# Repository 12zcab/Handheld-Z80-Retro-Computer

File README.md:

# A Handheld Z80 Retro Computer

Hello Im 12zcab from Hong Kong and I designed this Z80 Retro Computer :DD

# Zine Page
https://www.figma.com/design/0DzeSIebLkugrNq00bVcSF/Untitled?node-id=0-1&t=Gd1BAF2dvagKk23V-1

# Images

# What is this?
This is a portable handheld computer made with z80 customized for assembly language programming and simplified system for educational purpose.
The computer comtains a Z80 cpu,a SPI screen,a Esp32 C3 Supermini and 2 EEPROM slot,a RAM slot,a buzzer,some leds,2 7segments and a extendable port for IO.
The computer support Dual-UART communication, one with the Esp32 and one for extending.
# What it does?
It just let you run simple programs on it and let you bring it anywhere!
My final goal is to write a fully functional Operating System and make it as simple as possible on this computer!
With the ESP32 C3 Supermini connected through UART,you can draw on SPI screen and output characters just like connected to a VT100 Terminal (for old computers)
With the Buzzer,7segments and the keyboard also with the extendable port,you can build alsome retro coding projects on this old-fashion Cyberdeck :D
# Why it exists?
Erm it all started when I found a video about old pokemon games and i started to play Gen 1 pokemon games on emulators(Red Version).
I found it a really amazing experience to have play a game with greyscale and 8 bit musics.
Then I asked my parents and found that we actually have a real gameboy athome!!
I then started to research on how gameboy works and study on the Disassembled PokeRed gameboy assembly code on github and I was shocked on how elegance it is the original assembly code.
Then I learnt the gbz80 instruction set,also the boot rom of the gameboy,then also 8086,8051,8085 and z80 assembly.
I followed a youtube video and built my first z80 computer and started to do a few assembly programming on it and yah its really fun [Ytlink](https://youtu.be/A0VpPRWrqHc?si=ajm_OGpBwFbzzyzW).
I recently found Fallout Event on HackClub and instantly found this a great oppertunity to design my own real z80 computer that is simple and workable.

# Basic Structure
##Memory Map
| Address | Compoenent | Function |
|----|----|----|
|0x0000 - 0x7FFF| EEPROM | Executable Code of Operating System |
|0x8000 - 0xFEFF| RAM or EEPROM | Multibanked External EEPROM and RAM |
|0xFF00 - 0xFFFF| IO Outputs | for Output,UART,and also other Extension Usage |
|----|----|----|

# Compoenents

## Main Compoenents
| Name | Usage | Quantity |
|----|----|----|
| Z84C00xxP | The CPU of the Computer | 1 |
| ESP32 C3 Supermini | The Micro Controller Board for Serial Output Processing | 1 |
| 3.5inch SPI Screen 14Pin| For Displaying Serial Output | 1 |
| DS12885+ Clock Module | Clock Module For Z80 | 1 |
| 62256 | 32k RAM for Z80 | 1 |
| 28C256 | 32k EEPROM for External file and Bootloader and Applications | 2 |
| HDSP-7501 | 7 Segment Display for Z80 Output | 2 |
| 16550 | UART Communication IC for Z80 IO | 2 |
| PTS 810 SMD Button | Keyboard Input for Z80 | 64 |
| 4 Pin 6mm Switch | Reset Button for Z80 | 1 |
| LED SMD 1206 | SMD LED with internal resistor for Signal and Data Bus displaying | 39 |
| Buzzer | D12mm height 9.5mm with RM7.6mm Buzzer for ESP32 C3 Supermini to Emit sound when receive specific serial input from Z80 | 1 |
| CR2032 battery holder | Battery for DS12885+ Clock Module | 1 |

## Logic Gates and ICs
| Name | Usage | Quantity |
|----|----|----|
| 74HC573 | A Registor for Input and Output and Multibanking | 5 |
| 74HC04 | Hex Logic Invertor for toggling High-Activate Signals and Low-Activate Signals | 2 |
| 4068 | 8 Input AND/NAND Logic Gate for IO Signal Filtering | 1 |
| 74154 | 4 to 16 Decoder for IOS Address Decoding | 1 |
| 74HC00 | Quad NAND Gate | 2 |

## Crystals
| Name | Usage | Quantity |
|----|----|----|
| 4 Pin Crystals | 20MHz and 1.8432MHz for CPU and UART ic respectively | 2 |
| 2 Pin Crystal | 32768Hz for DS12885+ Clock Module | 1 |

## Resistors
| Name | Usage | Quantity |
|----|----|----|
| 1K resistor | 7 segment display resistor to prevent the display BURn :D | 2 |
| 10K resistor | Pull-up Resistors | 4 |

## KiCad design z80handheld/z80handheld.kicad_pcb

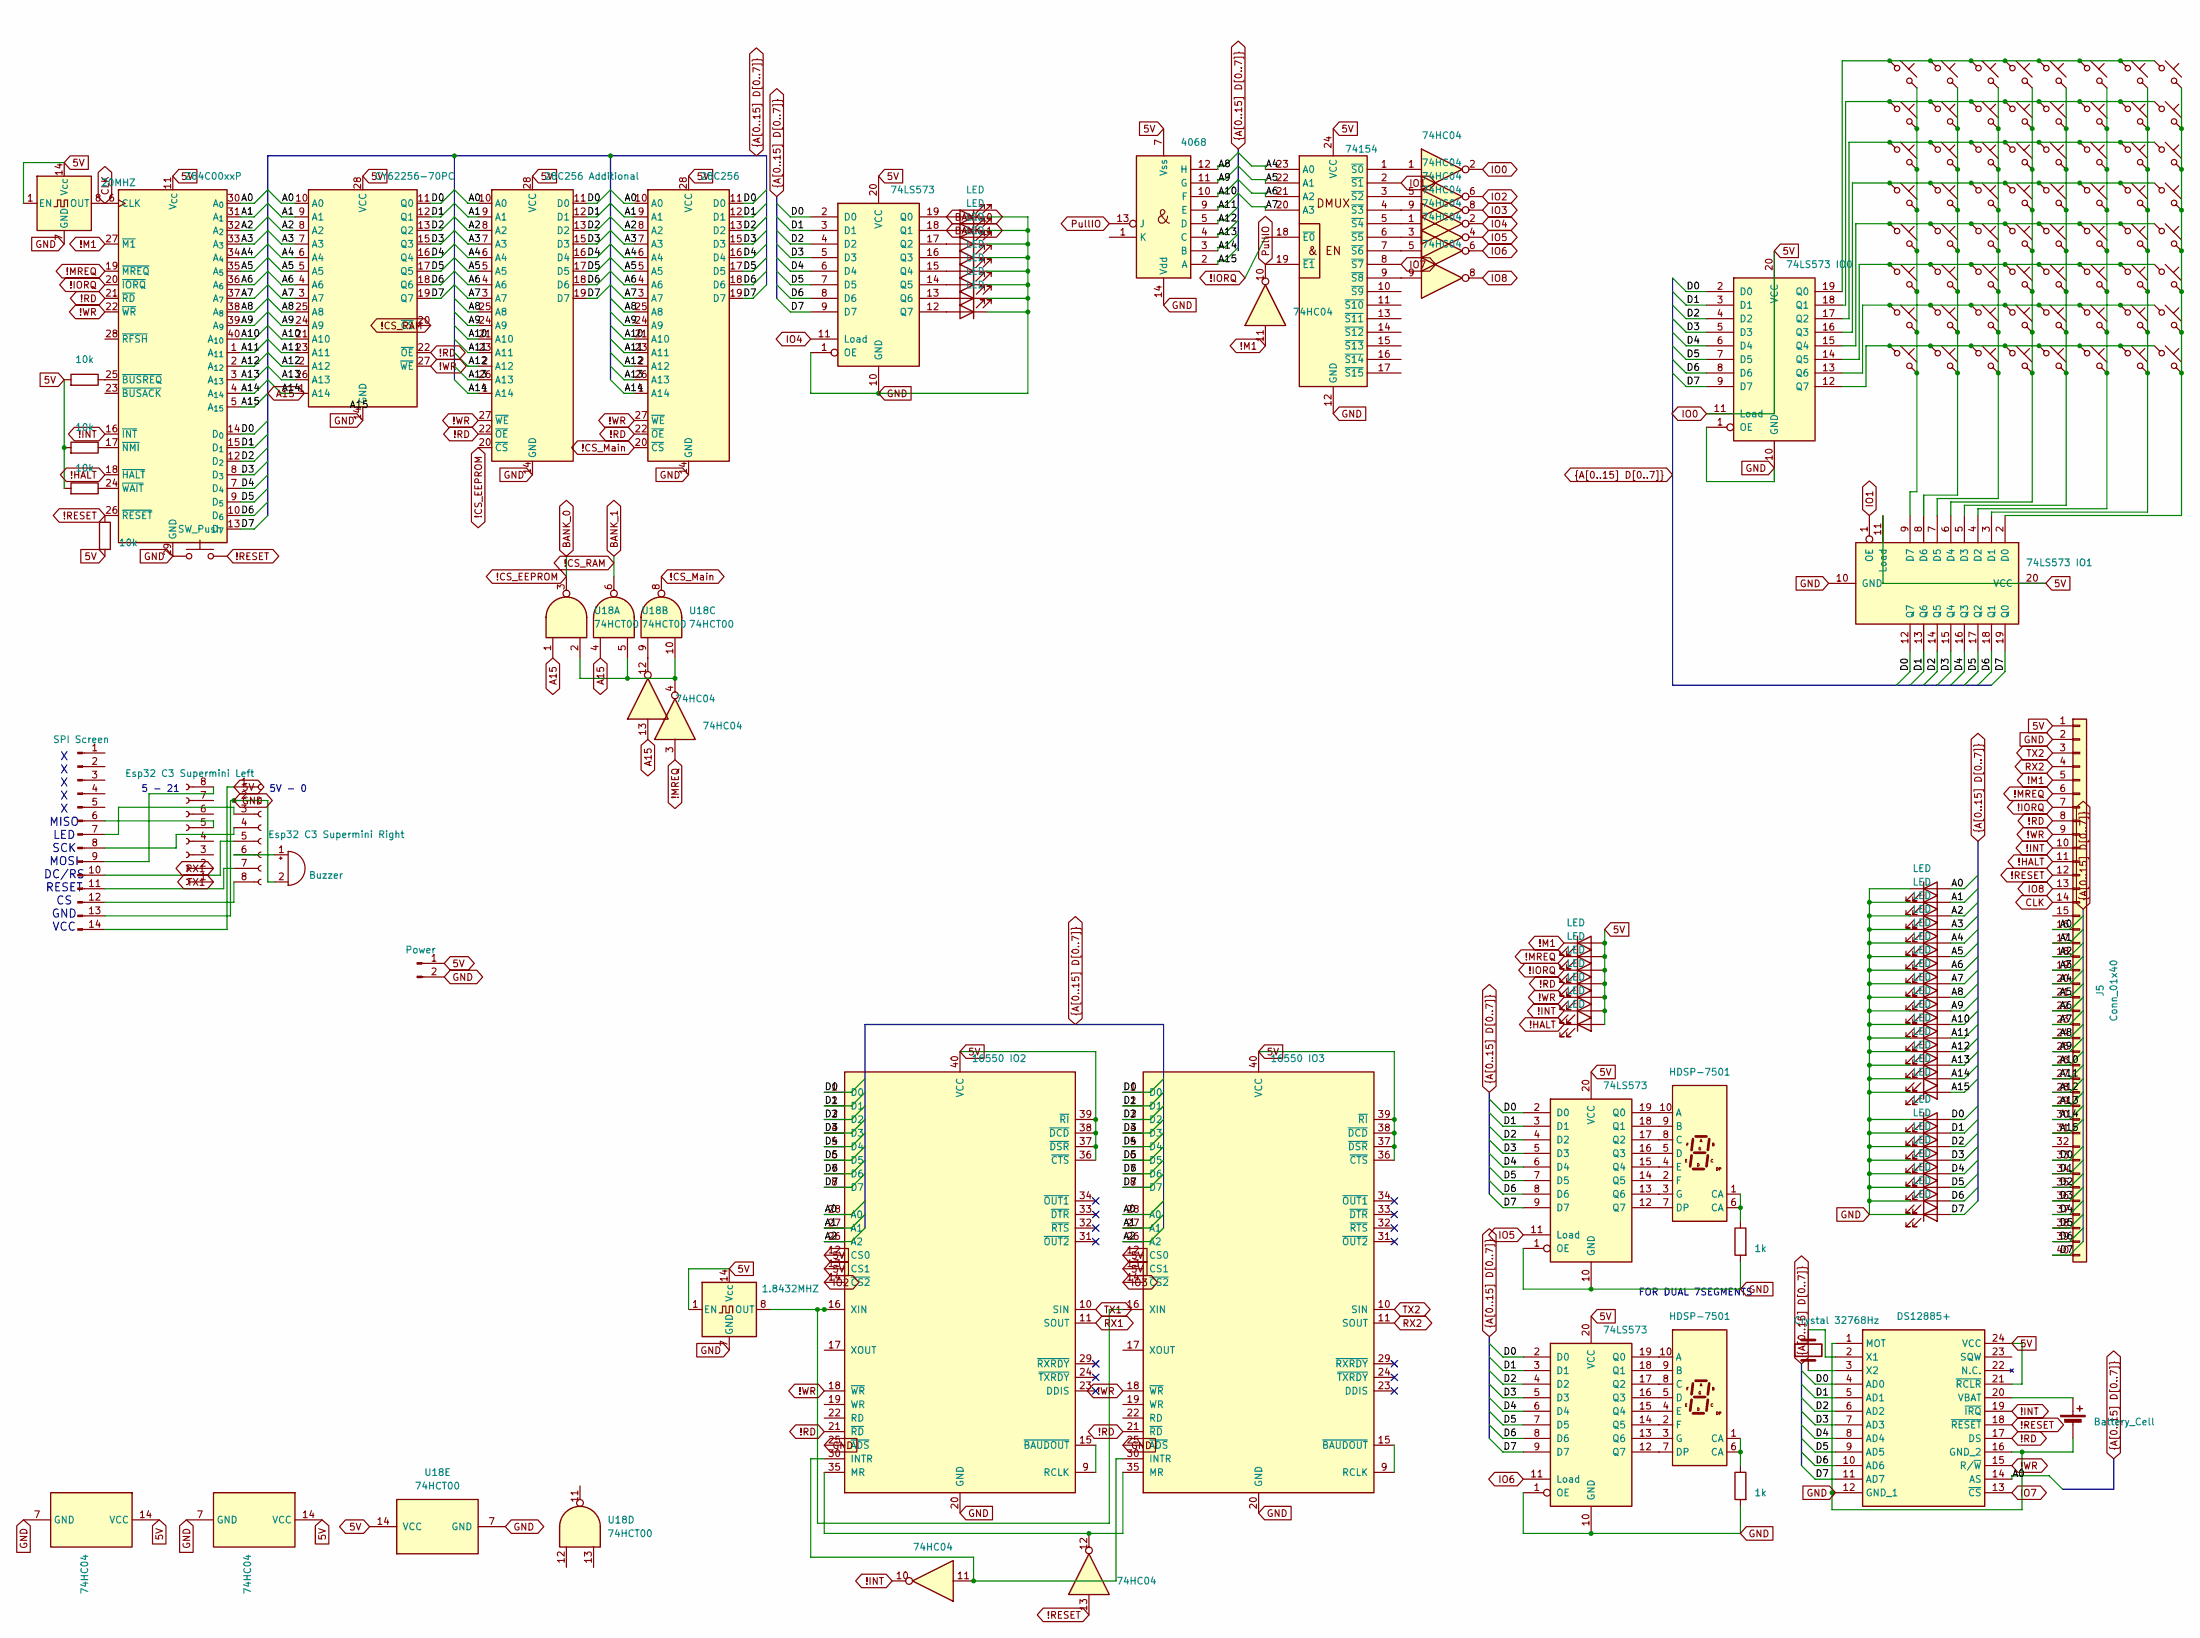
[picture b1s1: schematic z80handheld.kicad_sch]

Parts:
BT1: Battery_Cell; BatteryHolder_MYOUNG_BS-07-A1BJ001_CR2032
BZ1: Buzzer; Buzzer_12x9.5RM7.6
D1, D2, D3, D4, D5, D6, D7, D8, D9, D10, D11, D12, D13, D14, D15, D16, D17, D18, D19, D20, D21, D22, D23, D24, D25, D26, D27, D28, D29, D30, D31, D32, D33, D34, D35, D36, D37, D38, D39: LED; LED_1206_3216Metric_Pad1.42x1.75mm_HandSolder
IC1: DS12885+; DIP1524W51P254L3175H508Q24N; Manufacturer_Part_Number DS12885+; Mouser Part Number 700-DS12885
J1: Power; PinHeader_1x02_P2.54mm_Vertical
J2: Esp32 C3 Supermini Right; PinHeader_1x08_P2.54mm_Vertical
J3: SPI Screen; PinHeader_1x14_P2.54mm_Vertical
J4: Esp32 C3 Supermini Left; PinHeader_1x08_P2.54mm_Vertical
J5: Conn_01x40; PinHeader_1x40_P2.54mm_Vertical
R1, R2, R3, R5: 10k; R_Axial_DIN0207_L6.3mm_D2.5mm_P7.62mm_Horizontal
R4, R6: 1k; R_Axial_DIN0207_L6.3mm_D2.5mm_P7.62mm_Horizontal
SW1, SW2, SW3, SW4, SW5, SW6, SW7, SW8, SW9, SW10, SW11, SW12, SW13, SW14, SW15, SW16, SW17, SW18, SW19, SW20, SW21, SW22, SW23, SW24, SW25, SW26, SW27, SW28, SW29, SW30, SW31, SW32, SW33, SW34, SW35, SW36, SW37, SW38, SW39, SW40, SW41, SW42, SW43, SW44, SW45, SW46, SW47, SW48, SW49, SW50, SW51, SW52, SW53, SW54, SW55, SW56, SW57, SW58, SW59, SW60, SW61, SW62, SW63, SW64: SW_Push_45deg; SW_SPST_PTS810
SW65: SW_Push; SW_PUSH_6mm
U1, U3: 74HC04; DIP-14_W7.62mm
U2: 4068; DIP-14_W7.62mm
U4: 74154; DIP-24_W7.62mm
U5: 74LS573 IO0; DIP-20_W7.62mm
U6, U13, U15: 74LS573; DIP-20_W7.62mm
U7: CY62256-70PC; DIP_Socket-28_W6.9mm_W7.62mm_W10.16mm_W12.7mm_W13.5mm_3M_22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
U8: 28C256 Additional; DIP_Socket-28_W6.9mm_W7.62mm_W10.16mm_W12.7mm_W13.5mm_3M_22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
U9: 28C256; DIP_Socket-28_W6.9mm_W7.62mm_W10.16mm_W12.7mm_W13.5mm_3M_22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
U10: Z84C00xxP; DIP-40_W15.24mm
U11: 74LS573 IO1; DIP-20_W7.62mm
U12, U14: HDSP-7501; 7SegmentLED_LTS6760_LTS6780
U16: 16550 IO2; DIP-40_W15.24mm
U17: 16550 IO3; DIP-40_W15.24mm
U18: 74HCT00; DIP-14_W7.62mm
Y1: 20MHZ; Oscillator_DIP-14
Y2: Crystal 32768Hz; Crystal_C38-LF_D3.0mm_L8.0mm_Vertical
Y3: 1.8432MHZ; Oscillator_DIP-14

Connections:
5V: D6.2 (A), D9.2 (A), D12.2 (A), D15.2 (A), D18.2 (A), D21.2 (A), D24.2 (A), IC1.21 (~RCLR), IC1.24 (VCC), J1.1, J2.1, J3.14, J5.1, R1.1, R2.1, R3.1, R5.2, U1.2, U1.14 (VCC), U2.7 (Vss), U3.14 (VCC), U4.24 (VCC), U5.11 (Load), U5.20 (VCC), U6.20 (VCC), U7.28 (VCC), U8.28 (VCC), U9.28 (VCC), U10.11 (V_{CC}), U11.11 (Load), U11.20 (VCC), U13.20 (VCC), U15.20 (VCC), U16.12 (CS0), U16.13 (CS1), U16.36 (~CTS), U16.37 (~DSR), U16.38 (~DCD), U16.39 (~RI), U16.40 (VCC), U17.12 (CS0), U17.13 (CS1), U17.36 (~CTS), U17.37 (~DSR), U17.38 (~DCD), U17.39 (~RI), U17.40 (VCC), U18.14 (VCC), Y1.1 (EN), Y1.14 (Vcc), Y3.1 (EN), Y3.14 (Vcc)
!CS_EEPROM: D3.2 (A), U6.19 (Q0), U8.20 (~CS), U18.3
!CS_Main: U9.20 (~CS), U18.8
!CS_RAM: D5.2 (A), U6.18 (Q1), U7.20 (~CS), U18.6
!HALT: D6.1 (K), J5.11, U10.18 (~HALT)
!INT: D9.1 (K), IC1.19 (~IRQ), J5.10, U3.10, U10.16 (~INT)
!IORQ: D18.1 (K), J5.7, U4.18 (~E0), U10.20 (~IORQ)
!M1: D24.1 (K), J5.5, U1.11, U10.27 (~M1)
!MREQ: D21.1 (K), J5.6, U1.3, U10.19 (~MREQ)
!RD: D15.1 (K), IC1.17 (DS), J5.8, U7.22 (~OE), U8.22 (~OE), U9.22 (~OE), U10.21 (~RD), U16.21 (~RD), U17.21 (~RD)
!RESET: IC1.18 (~RESET), J5.12, R5.1, SW65.2, U3.13, U10.26 (~RESET)
!WR: D12.1 (K), IC1.15 (R/~W), J5.9, U7.27 (~WE), U8.27 (~WE), U9.27 (~WE), U10.22 (~WR), U16.18 (~WR), U17.18 (~WR)
/A0: D1.2 (A), IC1.14 (AS), J5.16, U7.10 (A0), U8.10 (A0), U9.10 (A0), U10.30 (A_{0}), U16.28 (A0), U17.28 (A0)
/A1: D2.2 (A), J5.17, U7.9 (A1), U8.9 (A1), U9.9 (A1), U10.31 (A_{1}), U16.27 (A1), U17.27 (A1)
/A2: D4.2 (A), J5.18, U7.8 (A2), U8.8 (A2), U9.8 (A2), U10.32 (A_{2}), U16.26 (A2), U17.26 (A2)
/A3: D7.2 (A), J5.19, U7.7 (A3), U8.7 (A3), U9.7 (A3), U10.33 (A_{3})
/A4: D10.2 (A), J5.20, U4.23 (A0), U7.6 (A4), U8.6 (A4), U9.6 (A4), U10.34 (A_{4})
/A5: D13.2 (A), J5.21, U4.22 (A1), U7.5 (A5), U8.5 (A5), U9.5 (A5), U10.35 (A_{5})
/A6: D16.2 (A), J5.22, U4.21 (A2), U7.4 (A6), U8.4 (A6), U9.4 (A6), U10.36 (A_{6})
/A7: D19.2 (A), J5.23, U4.20 (A3), U7.3 (A7), U8.3 (A7), U9.3 (A7), U10.37 (A_{7})
/A8: D22.2 (A), J5.24, U2.12 (H), U7.25 (A8), U8.25 (A8), U9.25 (A8), U10.38 (A_{8})
/A9: D25.2 (A), J5.25, U2.11 (G), U7.24 (A9), U8.24 (A9), U9.24 (A9), U10.39 (A_{9})
/A10: D26.2 (A), J5.26, U2.10 (F), U7.21 (A10), U8.21 (A10), U9.21 (A10), U10.40 (A_{10})
/A11: D27.2 (A), J5.27, U2.9 (E), U7.23 (A11), U8.23 (A11), U9.23 (A11), U10.1 (A_{11})
/A12: D28.2 (A), J5.28, U2.5 (D), U7.2 (A12), U8.2 (A12), U9.2 (A12), U10.2 (A_{12})
/A13: D29.2 (A), J5.29, U2.4 (C), U7.26 (A13), U8.26 (A13), U9.26 (A13), U10.3 (A_{13})
/A14: D30.2 (A), J5.30, U2.3 (B), U7.1 (A14), U8.1 (A14), U9.1 (A14), U10.4 (A_{14})
/D0: D32.2 (A), IC1.4 (AD0), J5.33, U5.2 (D0), U6.2 (D0), U7.11 (Q0), U8.11 (D0), U9.11 (D0), U10.14 (D_{0}), U11.12 (Q7), U13.2 (D0), U15.2 (D0), U16.1 (D0), U17.1 (D0)
/D1: D33.2 (A), IC1.5 (AD1), J5.34, U5.3 (D1), U6.3 (D1), U7.12 (Q1), U8.12 (D1), U9.12 (D1), U10.15 (D_{1}), U11.13 (Q6), U13.3 (D1), U15.3 (D1), U16.2 (D1), U17.2 (D1)
/D2: D34.2 (A), IC1.6 (AD2), J5.35, U5.4 (D2), U6.4 (D2), U7.13 (Q2), U8.13 (D2), U9.13 (D2), U10.12 (D_{2}), U11.14 (Q5), U13.4 (D2), U15.4 (D2), U16.3 (D2), U17.3 (D2)
/D3: D35.2 (A), IC1.7 (AD3), J5.36, U5.5 (D3), U6.5 (D3), U7.15 (Q3), U8.15 (D3), U9.15 (D3), U10.8 (D_{3}), U11.15 (Q4), U13.5 (D3), U15.5 (D3), U16.4 (D3), U17.4 (D3)
/D4: D36.2 (A), IC1.8 (AD4), J5.37, U5.6 (D4), U6.6 (D4), U7.16 (Q4), U8.16 (D4), U9.16 (D4), U10.7 (D_{4}), U11.16 (Q3), U13.6 (D4), U15.6 (D4), U16.5 (D4), U17.5 (D4)
/D5: D37.2 (A), IC1.9 (AD5), J5.38, U5.7 (D5), U6.7 (D5), U7.17 (Q5), U8.17 (D5), U9.17 (D5), U10.9 (D_{5}), U11.17 (Q2), U13.7 (D5), U15.7 (D5), U16.6 (D5), U17.6 (D5)
/D6: D38.2 (A), IC1.10 (AD6), J5.39, U5.8 (D6), U6.8 (D6), U7.18 (Q6), U8.18 (D6), U9.18 (D6), U10.10 (D_{6}), U11.18 (Q1), U13.8 (D6), U15.8 (D6), U16.7 (D6), U17.7 (D6)
/D7: D39.2 (A), IC1.11 (AD7), J5.40, U5.9 (D7), U6.9 (D7), U7.19 (Q7), U8.19 (D7), U9.19 (D7), U10.13 (D_{7}), U11.19 (Q0), U13.9 (D7), U15.9 (D7), U16.8 (D7), U17.8 (D7)
A15: D31.2 (A), J5.31, U1.13, U2.2 (A), U10.5 (A_{15}), U18.1, U18.4
CLK: J5.14, U10.6 (CLK), Y1.8 (OUT)
GND: BT1.2 (-), BZ1.2 (-), D1.1 (K), D2.1 (K), D3.1 (K), D4.1 (K), D5.1 (K), D7.1 (K), D8.1 (K), D10.1 (K), D11.1 (K), D13.1 (K), D14.1 (K), D16.1 (K), D17.1 (K), D19.1 (K), D20.1 (K), D22.1 (K), D23.1 (K), D25.1 (K), D26.1 (K), D27.1 (K), D28.1 (K), D29.1 (K), D30.1 (K), D31.1 (K), D32.1 (K), D33.1 (K), D34.1 (K), D35.1 (K), D36.1 (K), D37.1 (K), D38.1 (K), D39.1 (K), IC1.1 (MOT), IC1.12 (GND_1), IC1.16 (GND_2), J1.2, J2.2, J3.13, J5.2, R4.1, R6.1, SW65.1, U1.7 (GND), U2.14 (Vdd), U3.7 (GND), U4.12 (GND), U5.1 (OE), U5.10 (GND), U6.1 (OE), U6.10 (GND), U7.14 (GND), U8.14 (GND), U9.14 (GND), U10.29 (GND), U11.10 (GND), U13.1 (OE), U13.10 (GND), U15.1 (OE), U15.10 (GND), U16.20 (GND), U16.25 (~ADS), U17.20 (GND), U17.25 (~ADS), U18.7 (GND), Y1.7 (GND), Y3.7 (GND)
IO1: U4.2 (~S1), U11.1 (OE)
IO2: U1.6, U16.14 (~CS2)
IO3: U1.8, U17.14 (~CS2)
IO4: U3.2, U6.11 (Load)
IO5: U3.4, U13.11 (Load)
IO6: U3.6, U15.11 (Load)
IO7: IC1.13 (~CS), U4.8 (~S7)
IO8: J5.13, U3.8
unnamed: BT1.1 (+), IC1.20 (VBAT)
unnamed: BZ1.1 (+), J2.6
unnamed: D8.2 (A), U6.17 (Q2)
unnamed: D11.2 (A), U6.16 (Q3)
unnamed: D14.2 (A), U6.15 (Q4)
unnamed: D17.2 (A), U6.14 (Q5)
unnamed: D20.2 (A), U6.13 (Q6)
unnamed: D23.2 (A), U6.12 (Q7)
unnamed: IC1.2 (X1), Y2.2
unnamed: IC1.3 (X2), Y2.1
unnamed: J2.3, J3.7
unnamed: J2.4, J3.8
unnamed: J2.5, J3.10
unnamed: J2.7, J3.11
unnamed: J2.8, J3.12
unnamed: J3.6, J4.5
unnamed: J3.9, J4.8
unnamed: R4.2, U12.1 (CA), U12.6 (CA)
unnamed: R6.2, U14.1 (CA), U14.6 (CA)
unnamed: U1.4, U18.2, U18.5, U18.10
unnamed: U1.12, U18.9
unnamed: U1.1, U4.1 (~S0)
unnamed: U1.5, U4.3 (~S2)
unnamed: U1.9, U4.4 (~S3)
unnamed: U3.1, U4.5 (~S4)
unnamed: U3.3, U4.6 (~S5)
unnamed: U3.5, U4.7 (~S6)
unnamed: U3.9, U4.9 (~S8)
unnamed: SW1.1, SW2.1, SW3.1, SW4.1, SW5.1, SW6.1, SW7.1, SW8.1, U5.19 (Q0)
unnamed: SW9.1, SW10.1, SW11.1, SW12.1, SW13.1, SW14.1, SW15.1, SW16.1, U5.18 (Q1)
unnamed: SW17.1, SW18.1, SW19.1, SW20.1, SW21.1, SW22.1, SW23.1, SW24.1, U5.17 (Q2)
unnamed: SW25.1, SW26.1, SW27.1, SW28.1, SW29.1, SW30.1, SW31.1, SW32.1, U5.16 (Q3)
unnamed: SW33.1, SW34.1, SW35.1, SW36.1, SW37.1, SW38.1, SW39.1, SW40.1, U5.15 (Q4)
unnamed: SW41.1, SW42.1, SW43.1, SW44.1, SW45.1, SW46.1, SW47.1, SW48.1, U5.14 (Q5)
unnamed: SW49.1, SW50.1, SW51.1, SW52.1, SW53.1, SW54.1, SW55.1, SW56.1, U5.13 (Q6)
unnamed: SW57.1, SW58.1, SW59.1, SW60.1, SW61.1, SW62.1, SW63.1, SW64.1, U5.12 (Q7)
unnamed: R1.2, U10.25 (~BUSREQ)
unnamed: R2.2, U10.17 (~NMI)
unnamed: R3.2, U10.24 (~WAIT)
unnamed: SW8.2, SW16.2, SW24.2, SW32.2, SW40.2, SW48.2, SW56.2, SW64.2, U11.2 (D0)
unnamed: SW7.2, SW15.2, SW23.2, SW31.2, SW39.2, SW47.2, SW55.2, SW63.2, U11.3 (D1)
unnamed: SW6.2, SW14.2, SW22.2, SW30.2, SW38.2, SW46.2, SW54.2, SW62.2, U11.4 (D2)
unnamed: SW5.2, SW13.2, SW21.2, SW29.2, SW37.2, SW45.2, SW53.2, SW61.2, U11.5 (D3)
unnamed: SW4.2, SW12.2, SW20.2, SW28.2, SW36.2, SW44.2, SW52.2, SW60.2, U11.6 (D4)
unnamed: SW3.2, SW11.2, SW19.2, SW27.2, SW35.2, SW43.2, SW51.2, SW59.2, U11.7 (D5)
unnamed: SW2.2, SW10.2, SW18.2, SW26.2, SW34.2, SW42.2, SW50.2, SW58.2, U11.8 (D6)
unnamed: SW1.2, SW9.2, SW17.2, SW25.2, SW33.2, SW41.2, SW49.2, SW57.2, U11.9 (D7)
unnamed: U12.10 (A), U13.19 (Q0)
unnamed: U12.9 (B), U13.18 (Q1)
unnamed: U12.8 (C), U13.17 (Q2)
unnamed: U12.5 (D), U13.16 (Q3)
unnamed: U12.7 (DP), U13.12 (Q7)
unnamed: U12.4 (E), U13.15 (Q4)
unnamed: U12.2 (F), U13.14 (Q5)
unnamed: U12.3 (G), U13.13 (Q6)
unnamed: U14.10 (A), U15.19 (Q0)
unnamed: U14.9 (B), U15.18 (Q1)
unnamed: U14.8 (C), U15.17 (Q2)
unnamed: U14.5 (D), U15.16 (Q3)
unnamed: U14.7 (DP), U15.12 (Q7)
unnamed: U14.4 (E), U15.15 (Q4)
unnamed: U14.2 (F), U15.14 (Q5)
unnamed: U14.3 (G), U15.13 (Q6)
unnamed: U3.11, U16.30 (INTR), U17.30 (INTR)
unnamed: U3.12, U16.35 (MR), U17.35 (MR)
unnamed: U16.9 (RCLK), U16.15 (~BAUDOUT)
unnamed: U16.16 (XIN), U17.16 (XIN), Y3.8 (OUT)
unnamed: U17.9 (RCLK), U17.15 (~BAUDOUT)
PullIO: U1.10, U2.13 (J), U4.19 (~E1)
RX1: J4.2, U16.11 (SOUT)
RX2: J5.4, U17.11 (SOUT)
TX1: J4.1, U16.10 (SIN)
TX2: J5.3, U17.10 (SIN)

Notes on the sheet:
5V - 0
FOR DUAL 7SEGMENTS
5 - 21
X X X X X MISO LED SCK MOSI DC/RS RESET CS GND VCC

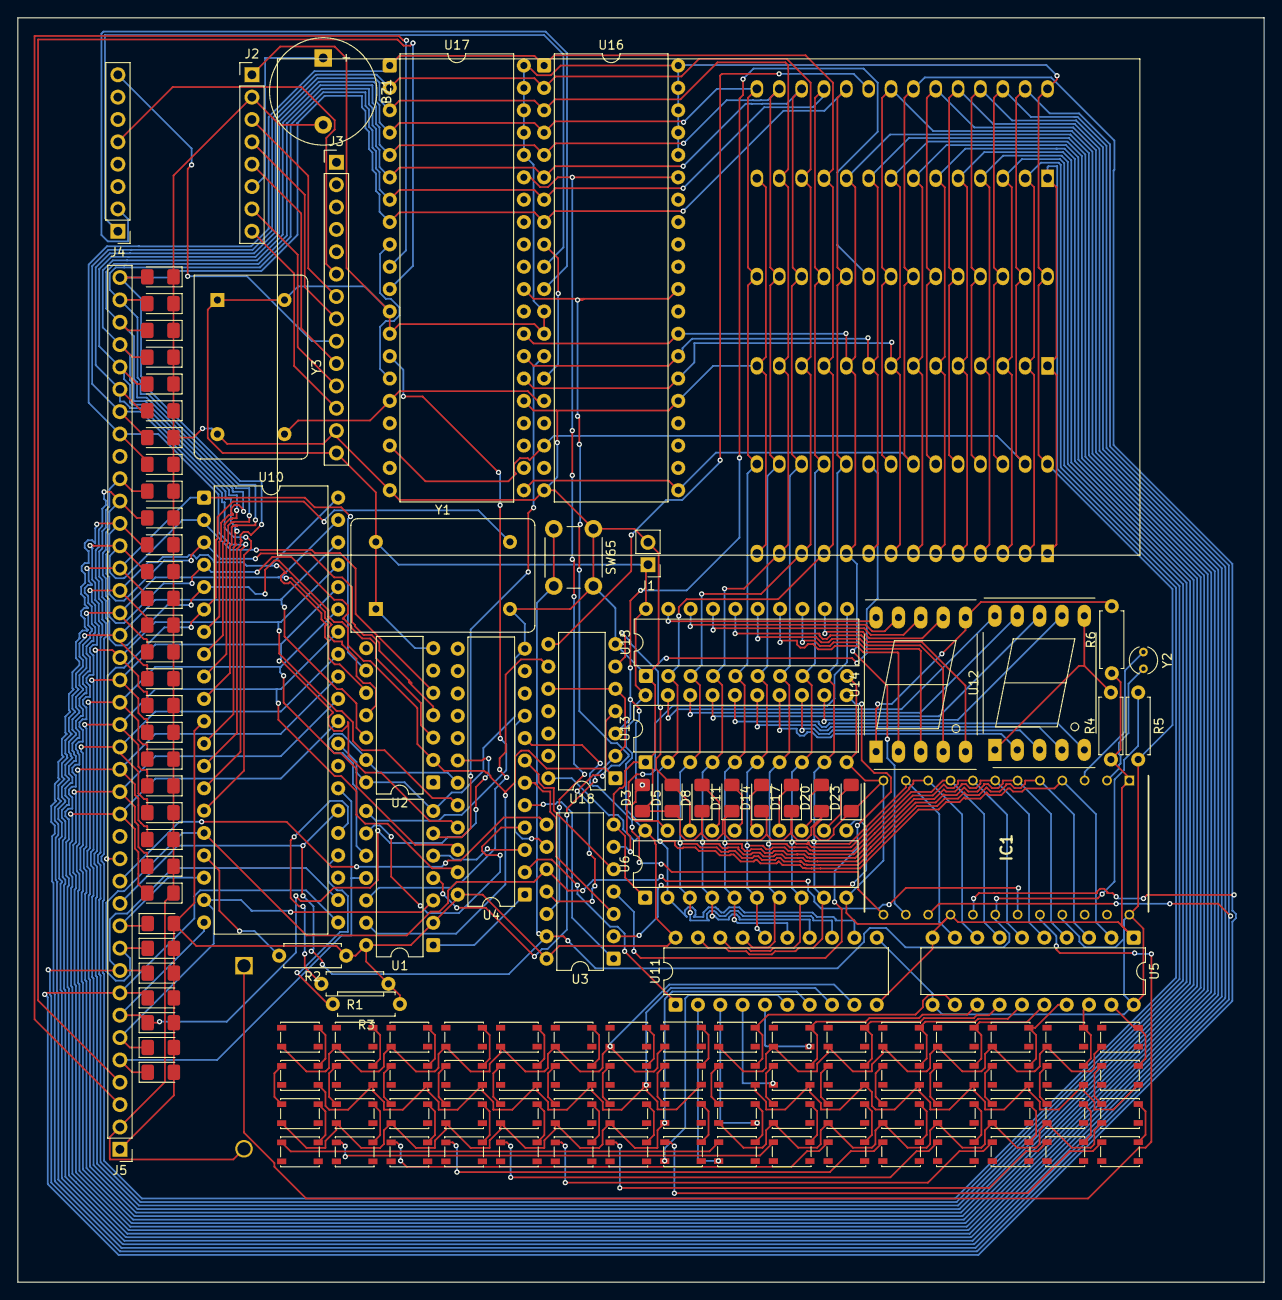
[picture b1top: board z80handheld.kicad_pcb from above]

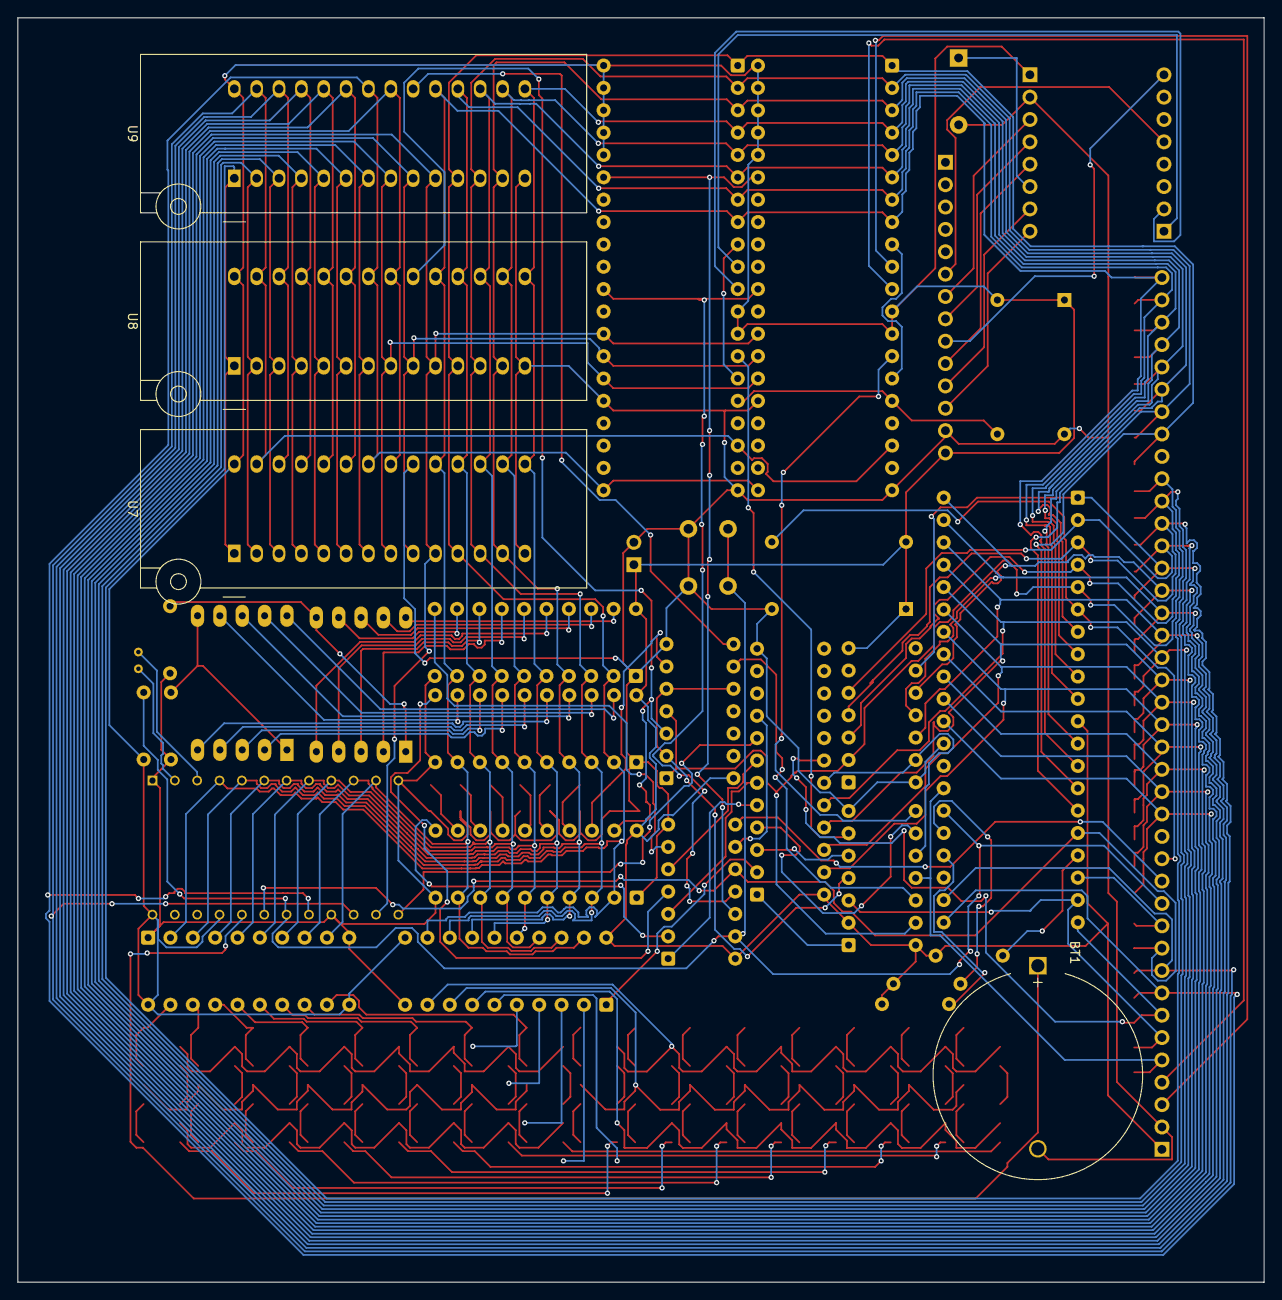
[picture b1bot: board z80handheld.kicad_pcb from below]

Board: 2 copper layers, 141.6 x 143.7 mm, 139 parts (4 on the bottom side), 119 nets.

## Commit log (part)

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2026-04-25 Create easteregg
2026-04-25 Rename 螢幕擷取畫面 (103).png to design.png
2026-04-25 Rename 螢幕擷取畫面 (107).png to Route.png
2026-04-25 Rename 螢幕擷取畫面 (110).png to PCB.png
2026-05-07 Add LoadFromAToB assembly routine
    This assembly code loads data from one memory location to another using a loop.
2026-05-07 Initialize stack pointer in 7segment.z80
    Initialize the stack pointer before outputting to the 7-segment display.
2026-05-24 Revise README for improved clarity and formatting
    Updated README to enhance clarity and structure, including a detailed list of components and functionalities.
2026-06-13 Create eastereggagain
